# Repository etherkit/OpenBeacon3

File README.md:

OpenBeacon 3
============
500 mW Si5351C-based MEPT Transmitter

Display
-------
Line 1: GPS status (internal or external antenna, number of satellites fixed), UTC time, transmission mode

Line 2: Frequency

Line 3: PA current, input voltage

Line 4: Message buffer contents

Line 5: Button functions

LEDs
----
* **D1** (red)

    Transmit<br />
    UART TX (during firmware loading)  

* **D2** (green)

    UART RX (during firmware loading)
    
* **D3** (blue)

    PA enabled

* **D5** (yellow)

    Power

User Interface
--------------
* **Tuning**

    Turn S4 rotary encoder to tune
    
* **Tuning Rate**

    Depress rotary encoder shaft momentarily to step through tuning rates. An underline cursor will indicate which frequency digit is being changed.
    
* **Change Band or Mode**

    Hold rotary encoder shaft in for 1 second to access the band and mode change menu. Turn the rotary encoder to cycle between selections. Press button S1 to change the band selection or press button S2 to change the mode selection. Press button S3 to exit this menu.

* **Configuration Menu (S1)**

    Not yet implemented
    
* **Start/Stop (S2)**

    Press button to immediately start a transmission if the transmitter is currently idle, or immediately stop a transmission if one is currently active.
    
* **TX Enb/TX Dis (S3)**

    Press button to toggle the state of recurring transmissions.

Message Buffer System
---------------------
When using the CW, QRSS, DFCW, and Hell modes, five different message buffers are available for transmission. Message Buffer 0 is a special case and consists solely of the value set in the ```callsign``` configuration variable. Message Buffers 1 through 4 can be set to any 40 character (consisting of letters, numbers, or characters ```/```, ```=```, and ```?```) user message via the configuration system. OpenBeacon 2 can be set transmit the contents of any of the five message buffers during a transmit period.

In WSPR mode, OpenBeacon 2 uses the callsign specified in the ```callsign``` configuration variable, the current Maidenhead grid square as determined from GPS (or the default value placed in the ```grid``` configuration variable if the GPS does not have a location fix), and the power level specified in the  ```dbm``` configuration variable.

Recurring Transmissions
-----------------------

Configuration
-------------
The configuration for OpenBeacon 2 is loaded via the included USB-UART bridge. To send configuration data, send OpenBeacon 2 a string consisting of the character 'W', followed by a JSON string setting the desired conifiguration variables, followed by a '@' termination character. For example:

    W{"callsign":"W1AW","default_buffer":2,"msg_mem_2":"HELLO WORLD"}@
    
Here is the list of available configuration variables:

* **default_buffer**
* **msg_mem_1**
* **msg_mem_2**
* **msg_mem_3**
* **msg_mem_4**
* **callsign**
* **grid**
* **dbm**
* **ext_gps_ant**
* **ext_pll_ref**
* **ext_pll_ref_freq**

Required Libraries
------------------
Install these library from the indicated locations before attempting to compile and upload your own firmware.

* Flash Storage [https://github.com/cmaglie/FlashStorage](https://github.com/cmaglie/FlashStorage)
* TinyGPS++ [http://arduiniana.org/libraries/tinygpsplus/](http://arduiniana.org/libraries/tinygpsplus/)
* Etherkit SSD1306 [https://github.com/etherkit/SSD1306-Arduino](https://github.com/etherkit/SSD1306-Arduino)
* Etherkit Si5351 (Library Manager)
* Etherkit JTEncode (Library Manager)
* Scheduler (Library Manager)
* ArduinoJson (Library Manager)
* SPI (Arduino Standard Library)
* Wire (Arduino Standard Library)

Updating the Firmware
---------------------
Connect OpenBeacon 2 to your PC via USB. In the Arduino IDE, select board type ```Arduino/Genuino Zero (Native USB Port)``` and the correct virtual serial port. Sketches can be uploaded to OpenBeacon 2 as if it were a standard Arduino Zero (although a custom hardware configuration is coming soon).

TODO
----
  - [ ] Internal/External Ref Osc
  - [ ] Internal/External GPS Antenna
  - [ ] Get Hell mode working

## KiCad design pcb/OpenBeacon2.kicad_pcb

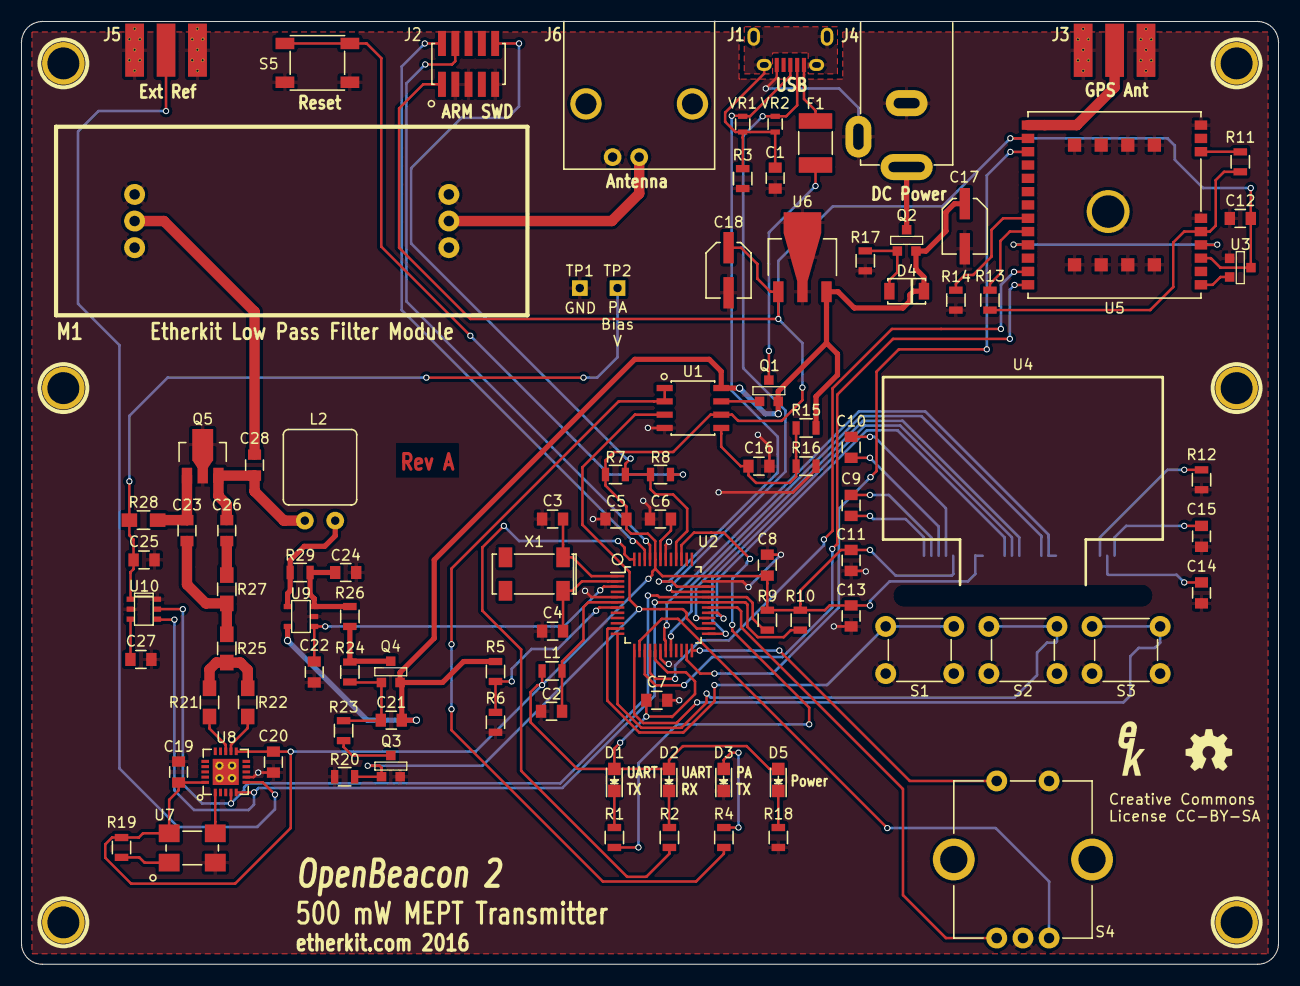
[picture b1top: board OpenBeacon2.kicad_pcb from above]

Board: 2 copper layers, 120.0 x 90.0 mm, 104 parts (0 on the bottom side), 79 nets.

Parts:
1PIN, 1PIN#2, 1PIN#3, 1PIN#4, 1PIN#5, 1PIN#6: P***; MOUNTINGHOLE-4MM
C1: 4.7n; C_0805
C2, C14: 4.7u; C_0805
C3, C4: 6.8; C_0805
C5, C7, C8, C11, C12, C13, C19, C20, C22, C27: 100n; C_0805
C6, C9, C10, C24, C25: 1u; C_0805
C15: 2.2u; C_0805
C16, C21, C23, C26, C28: 10n; C_0805
C17, C18: 10u; CAP-ELEC-5MM
D1: Red; Lite-On_LTST-C170
D2: Yellow; Lite-On_LTST-C170
D3: Blue; Lite-On_LTST-C170
D4: BZV55-B15; SOD80
D5: Green LED; Lite-On_LTST-C170
F1: MF-MSMF050-2; Bournes_MF-MSMF050-2
J1: USB Micro; FCI_10118194-0001LF
J2: ARM_SWD; FCI_20021121-00010C4LF
J3, J5: SMA-F; SMA-ENDLAUNCH
J4: 2.1mm Barrel Jack; DCPOWER-KOBICONN-163-7620-E
J6: BNC; BNC-AMPHENOL-31-5431-10RFX
L1: 10uH; R_0805
L2: FB2402-61 5T; BN2402-H
M1: Etherkit Low Pass Filter Module; LPFModule
Q1, Q2: IRLML9301; SOT23-2N7002
Q3: 2N7002; SOT23-2N7002
Q4: MMBT4403; SOT23-MMBT440X
Q5: RD00HVS1
R1, R2, R4, R8, R18: 330; R_0805
R3: 1M; R_0805
R5: 22k 1%; R_0805
R6: 4.7k 1%; R_0805
R7, R11: 10k; R_0805
R9, R10: 4.7k; R_0805
R12: 390k; R_0805
R13, R14: 2.2k; R_0805
R15, R16, R17: 100k; R_0805
R19: 0; R_0805
R20, R23, R24: 22k; R_0805
R21, R22, R25: 18; R_0805_HandSoldering
R26: 10; R_0805
R27: 3.3k; R_0805_HandSoldering
R28: 56; R_0805_HandSoldering
R29: 0.5 1%; R_0805
Ref**: Val**; EtherkitLogoSmall
S1, S2, S3: Reset; Omron_B3F-1052
S4: ENCODER-SW; Bournes_PEC12R-4225F-S0024
S5: Reset; Alps_SKQGAKE010
TP1: GND; Measurement_Point_Square-TH_Small
TP2: BIAS V; Measurement_Point_Square-TH_Small
U1: LM358; SOIC-8_3.9x4.9mm_Pitch1.27mm
U2: ATSAMD21G18A; TQFP-48_7x7mm_Pitch0.5mm
U3: MAX809; SOT23-MAX809
U4: ER-OLED0.96-1W; EastRising_ER-OLED0.96-1W-Thru
U5: A2235-H
U6: ZLDO1117G33TA; SOT-223-3
U7: FOX924B-25.000; Fox_924B
U8: Si5351C; QFN-20-1EP_4x4mm_Pitch0.5mm
U9: INA193; SOT23-5
U10: MCP4725A1T-E/CH; SOT23-6
VR1, VR2: CG0603MLC-05E; R_0603
X1: ABS25-32.768KHz-6-1-T; Abracon_ABS25

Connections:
1.8V: R11.1, R13.1, U5.5
+3.3VREG: C5.1, C7.1, C8.1, C11.1, C12.1, C13.1, C18.1, C19.1, C20.1, D1.1, D2.1, D5.1, J2.1, L1.1, R7.2, R9.1, R10.1, R19.1, U1.6, U2.17, U2.36, U2.44, U3.3, U4.6, U4.9, U4.10, U5.3, U5.11, U6.1, U7.4, U8.11, U8.20
/Logic/VUSB: F1.2, Q1.3
A0: C22.1, U2.3, U9.1
A1: R5.2, R6.1, U2.7
D0/UART_RX: U2.16, U5.21
D1/UART_TX: U2.15, U5.22
D2: U2.23, U5.12
D3: S4.3, U2.14
D4: S3.3, S3.4, U2.13
D5: S4.5, U2.24
D6: U2.29, U4.13
D7: S4.1, U2.30
D8: S1.3, S1.4, U2.11
D9: S2.3, S2.4, U2.12
D11: U2.25, U4.14
D12: U2.28, U4.15
D13: Q3.2, R20.1, U1.3, U2.26
DM: J1.2, U2.33, VR2.1
DP: J1.3, U2.34, VR1.1
GND: C1.1, C2.2, C3.1, C4.1, C5.2, C6.1, C7.2, C8.2, C11.2, C12.2, C13.2, C14.2, C15.2, C16.2, C17.2, C18.2, C19.2, C20.2, C22.2, C24.2, C25.2, C27.2, D3.2, J1.5, J2.3, J2.5, J2.9, J3.2, J4.2, J4.3, J5.2, J6.2, M1.1, M1.3, M1.4, M1.6, Q3.1, Q5.1, R3.1, R6.2, R12.2, R14.1, R16.2, R17.2, R18.2, R20.2, S1.1, S1.2, S2.1, S2.2, S3.1, S3.2, S4.2, S4.4, S5.3, S5.4, TP1.1, U1.4, U2.5, U2.18, U2.35, U2.42, U3.1, U4.1, U4.8, U4.11, U4.12, U4.16, U4.17, U4.21, U4.22, U4.23, U4.24, U4.25, U4.29, U4.30, U5.6, U5.9, U5.23, U5.24, U5.25, U5.26, U5.27, U5.28, U5.29, U5.30, U6.2, U7.2, U8.7, U8.21, U9.2, U10.2, U10.6
unnamed: C1.2, J1.6, R3.2, VR1.2, VR2.2
unnamed: C2.1, L1.2, U2.6
unnamed: C3.2, U2.1, X1.1
unnamed: C4.2, U2.2, X1.4
unnamed: C6.2, U2.43
unnamed: C9.1, U4.2
unnamed: C9.2, U4.3
unnamed: C10.1, U4.4
unnamed: C10.2, U4.5
unnamed: C14.1, U4.27
unnamed: C15.1, U4.28
unnamed: C16.1, R15.2, R16.1, U1.5
unnamed: C21.2, Q4.2, R23.1, R24.2
unnamed: C23.1, Q5.2, R28.1
unnamed: C23.2, R25.1, R27.2
unnamed: C24.1, R26.1, R29.2, U9.3
unnamed: C25.1, R28.2, TP2.1, U10.1
unnamed: C26.1, C28.2, L2.2, Q5.3
unnamed: C26.2, R27.1
unnamed: C27.1, U10.3
unnamed: C28.1, M1.2
unnamed: D1.2, R1.1
unnamed: D2.2, R2.1
unnamed: D3.1, R4.2
unnamed: D4.1, Q2.2, R17.1
unnamed: D5.2, R18.1
unnamed: F1.1, J1.1
unnamed: J3.1, U5.10
unnamed: J4.1, Q2.3
unnamed: J5.1, U8.6
unnamed: J6.1, M1.5
unnamed: L2.1, R29.1, U9.4
unnamed: Q1.2, U1.7
unnamed: Q3.3, R23.2
unnamed: Q4.3, R24.1, R26.2
unnamed: R4.1, U1.1, U1.2
unnamed: R8.1, S5.1, S5.2
unnamed: R11.2, U5.7
unnamed: R12.1, U4.26
unnamed: R13.2, U5.18
unnamed: R14.2, U5.17
unnamed: R19.2, U7.1
unnamed: R21.1, R22.1, R25.2
unnamed: R21.2, U8.13
unnamed: R22.2, U8.12
unnamed: U3.2, U5.1
unnamed: U7.3, U8.1
RESET: J2.10, R7.1, R8.2, U2.40
RX_LED: R2.2, U2.48
SCL: R9.2, U2.32, U8.4, U10.5
SDA: R10.2, U2.31, U8.5, U10.4
SPI_MOSI: U2.19, U4.19, U4.20
SPI_SCK: U2.20, U4.18
SWDCLK: J2.4, U2.45
SWDIO: J2.2, U2.46
TX_LED: R1.2, U2.39
VDD: C17.1, C21.1, D4.2, Q1.1, Q2.1, Q4.1, R5.1, R15.1, U1.8, U6.3, U9.5
WAKEUP: U5.4, U5.19

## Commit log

2016-02-11 Add band and mode selection
2016-02-24 Rudimentary documenation in README
2016-02-28 Support external PLL reference and set ref frequency in init()
2016-03-03 Change ADC resolution to 12-bits
2016-03-05 test
2016-03-07 basic fixes
2019-09-17 Change to OpoenBeacon 3

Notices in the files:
pcb/OpenBeacon2.kicad_pcb:
Creative Commons License CC-BY-SA
